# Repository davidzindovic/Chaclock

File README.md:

# Ambiental-Clock
A LED based clock that runs on the ESP8266 microcontroller. 
The 12 numbers light up depending on the time (approximation of 5 min), while the main 9 segment "picture" includes a color fade depending on the time of day.
The code includes a sleep mode , which resets the uC entirely in order to prevent the timer overflow. 
(in order to prevent any visible change upon reset - since it will most likely happen during the night)
The clock fades on sometime during the morning and fades off at a certain point during nightime.

The colors and silhuette are meant to simbolize a meditating person, relating to chakras - hence the name Chaclock.

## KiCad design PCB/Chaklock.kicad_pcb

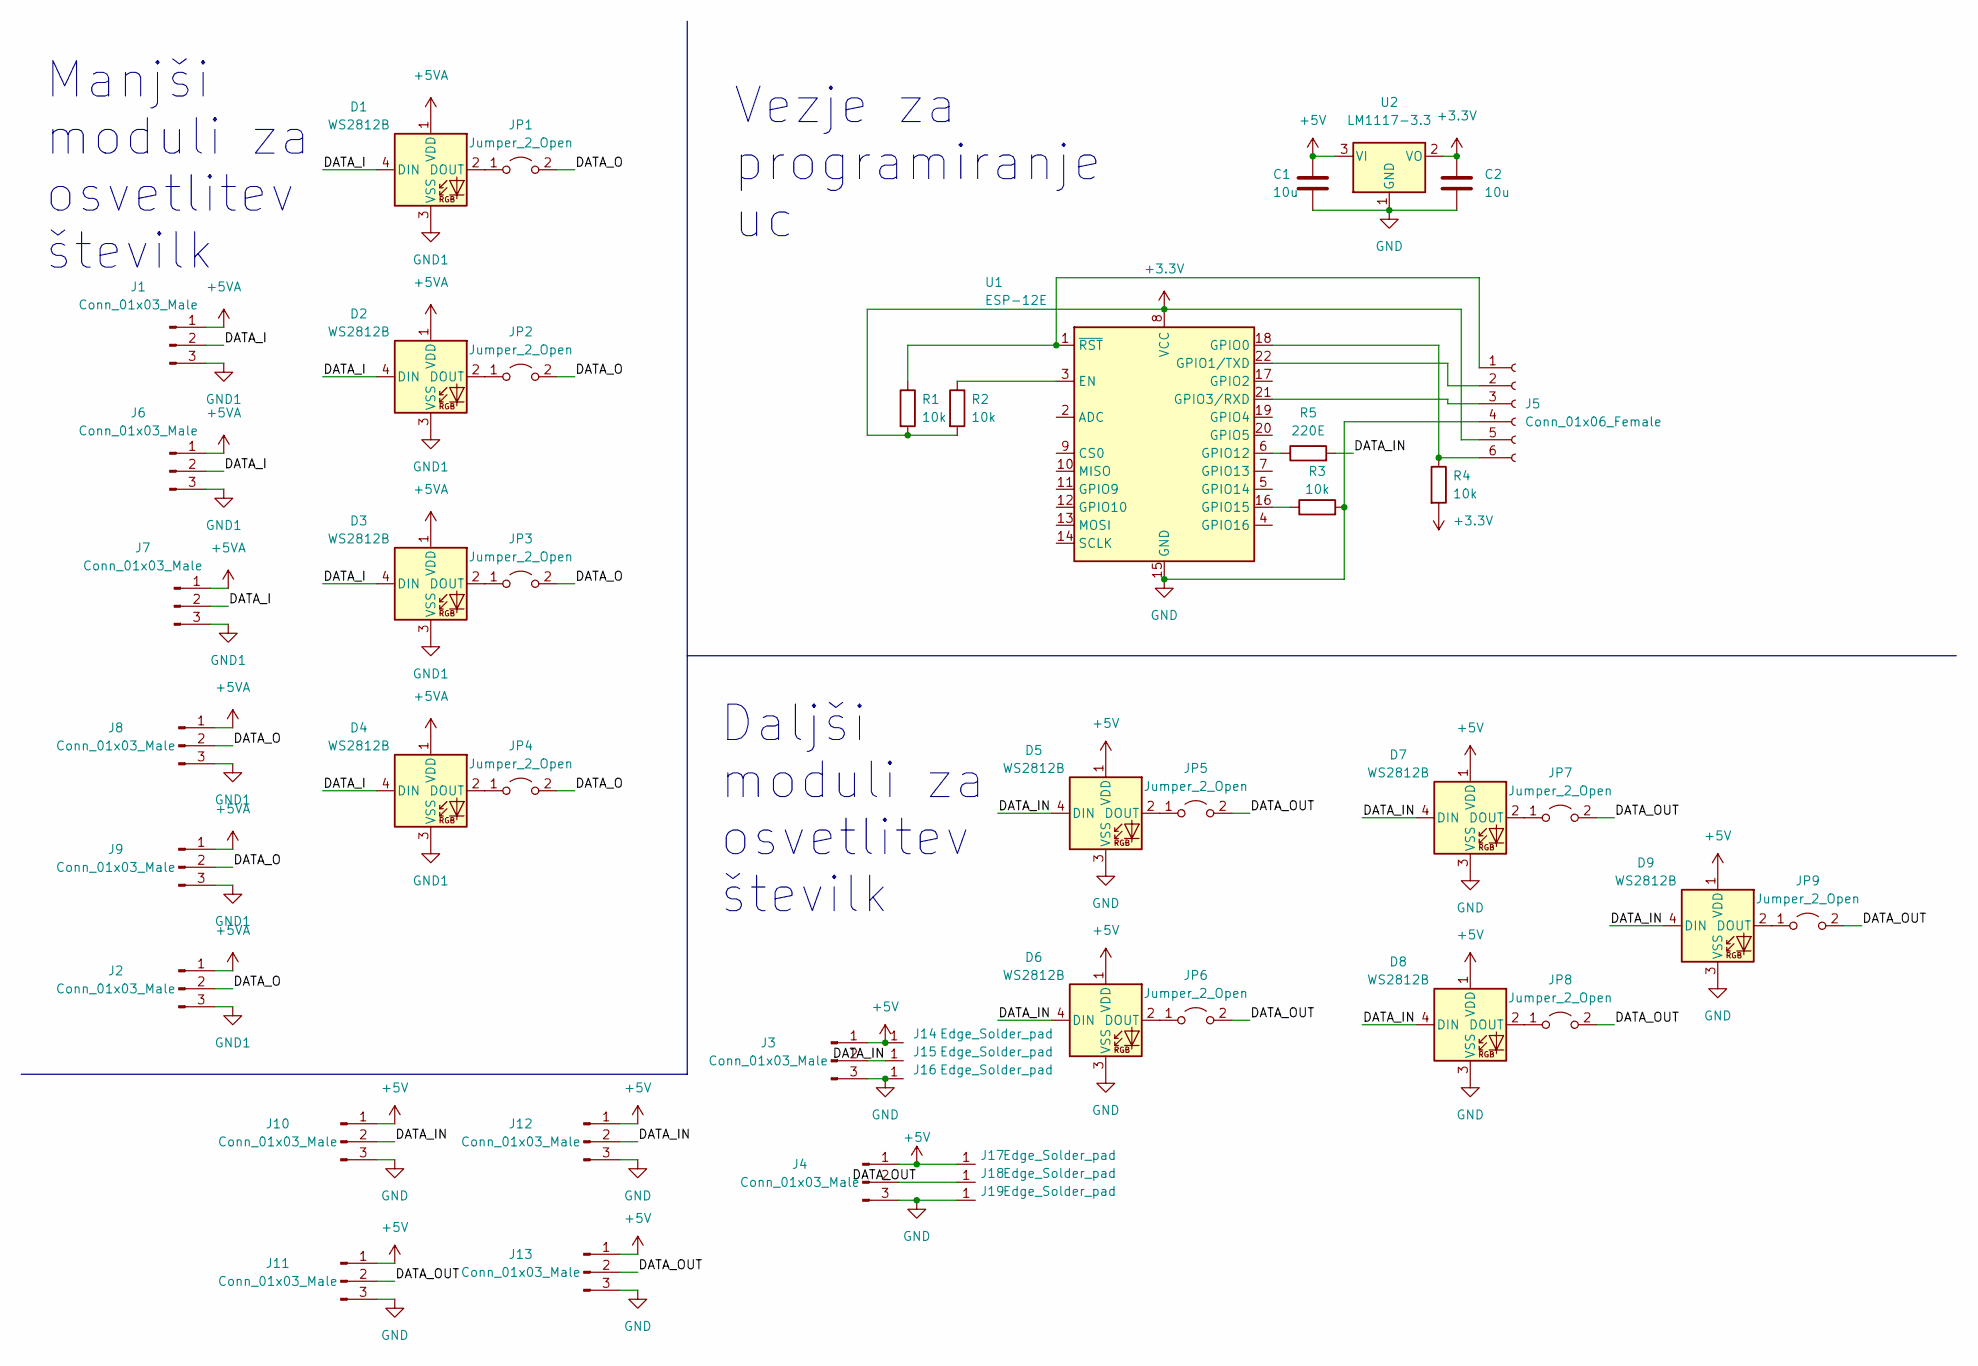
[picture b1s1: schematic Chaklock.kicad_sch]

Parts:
C1, C2: 10u; C_Disc_D5.0mm_W2.5mm_P5.00mm
D1, D2, D3, D4, D5, D6, D7, D8, D9: WS2812B; LED_WS2812B_PLCC4_5.0x5.0mm_P3.2mm
J1, J2, J3, J4, J6, J7, J8, J9, J10, J11, J12, J13: Conn_01x03_Male; PinHeader_1x03_P2.54mm_Vertical
J5: Conn_01x06_Female; PinHeader_1x06_P2.54mm_Vertical
J14, J15, J16, J17, J18, J19: Edge_Solder_pad; Edge Solder pad
JP1, JP2, JP3, JP4, JP5, JP6, JP7, JP8, JP9: Jumper_2_Open; SolderJumper-2_P1.3mm_Open_TrianglePad1.0x1.5mm
R1, R2, R3, R4: 10k; R_0805_2012Metric
R5: 220E; R_0805_2012Metric
U1: ESP-12E
U2: LM1117-3.3; TO-252-3_TabPin2

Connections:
+3.3V: C2.1, J5.5, R1.2, R2.2, R4.2, U1.8 (VCC), U2.2 (VO)
+5V: C1.1, D5.1 (VDD), D6.1 (VDD), D7.1 (VDD), D8.1 (VDD), D9.1 (VDD), J3.1, J4.1, J10.1, J11.1, J12.1, J13.1, J14.1, J17.1, U2.3 (VI)
+5VA: D1.1 (VDD), D2.1 (VDD), D3.1 (VDD), D4.1 (VDD), J1.1, J2.1, J6.1, J7.1, J8.1, J9.1
/DATA_I: D1.4 (DIN), D2.4 (DIN), D3.4 (DIN), D4.4 (DIN), J1.2, J6.2, J7.2
/DATA_IN: D5.4 (DIN), D6.4 (DIN), D7.4 (DIN), D8.4 (DIN), D9.4 (DIN), J3.2, J10.2, J12.2, J15.1, R5.2
/DATA_O: J2.2, J8.2, J9.2, JP1.2 (B), JP2.2 (B), JP3.2 (B), JP4.2 (B)
/DATA_OUT: J4.2, J11.2, J13.2, J18.1, JP5.2 (B), JP6.2 (B), JP7.2 (B), JP8.2 (B), JP9.2 (B)
GND: C1.2, C2.2, D5.3 (VSS), D6.3 (VSS), D7.3 (VSS), D8.3 (VSS), D9.3 (VSS), J3.3, J4.3, J5.4, J10.3, J11.3, J12.3, J13.3, J16.1, J19.1, R3.2, U1.15 (GND), U2.1 (GND)
GND1: D1.3 (VSS), D2.3 (VSS), D3.3 (VSS), D4.3 (VSS), J1.3, J2.3, J6.3, J7.3, J8.3, J9.3
unnamed: D1.2 (DOUT), JP1.1 (A)
unnamed: D2.2 (DOUT), JP2.1 (A)
unnamed: D3.2 (DOUT), JP3.1 (A)
unnamed: D4.2 (DOUT), JP4.1 (A)
unnamed: D5.2 (DOUT), JP5.1 (A)
unnamed: D6.2 (DOUT), JP6.1 (A)
unnamed: D7.2 (DOUT), JP7.1 (A)
unnamed: D8.2 (DOUT), JP8.1 (A)
unnamed: D9.2 (DOUT), JP9.1 (A)
unnamed: J5.1, R1.1, U1.1 (~RST)
unnamed: J5.2, U1.22 (GPIO1/TXD)
unnamed: J5.3, U1.21 (GPIO3/RXD)
unnamed: J5.6, R4.1, U1.18 (GPIO0)
unnamed: R2.1, U1.3 (EN)
unnamed: R3.1, U1.16 (GPIO15)
unnamed: R5.1, U1.6 (GPIO12)

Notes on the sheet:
Vezje za programiranje uc
Daljši moduli za osvetlitev številk
Manjši moduli za osvetlitev številk

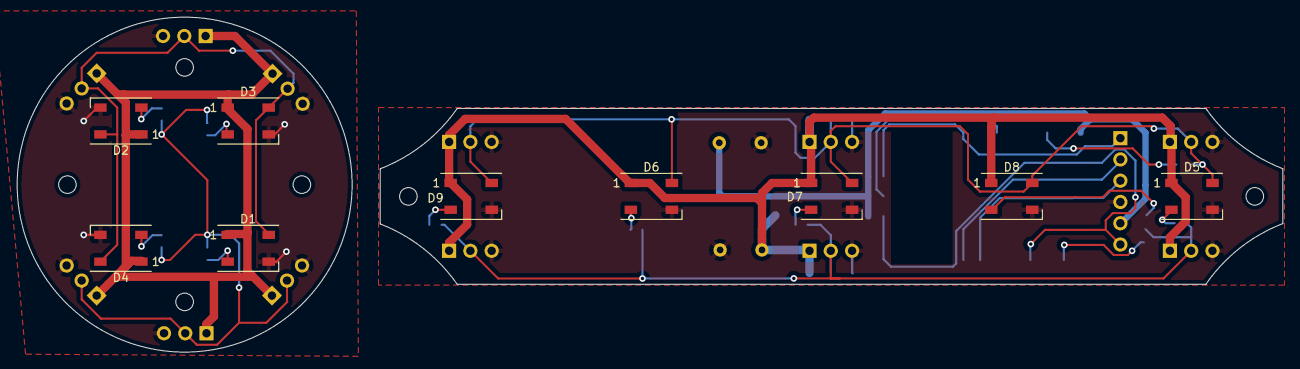
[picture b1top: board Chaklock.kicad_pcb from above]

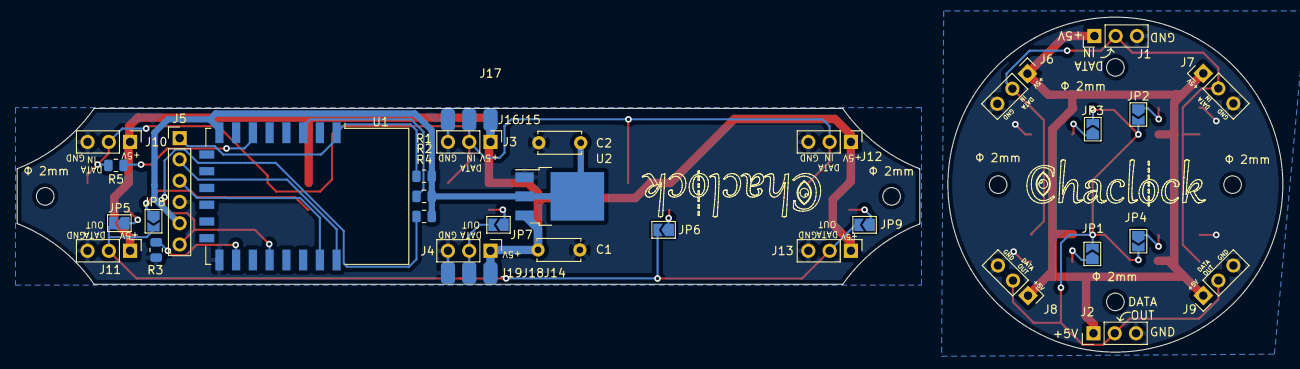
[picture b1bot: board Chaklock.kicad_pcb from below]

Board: 2 copper layers, 151.2 x 40.0 mm, 52 parts (37 on the bottom side), 25 nets.

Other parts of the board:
Ф 2mm, Ф 2mm#2, Ф 2mm#3, Ф 2mm#4, Ф 2mm#5, Ф 2mm#6: MountingHole_2.1mm

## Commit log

2021-12-26 Create main_code
2022-11-18 Update main_code
2025-06-13 Rename Logo.dxf to Graphics/Logo.dxf
2025-06-13 Rename Logo2.dxf to Graphics/Logo2.dxf
2025-06-13 Rename Logo3.dxf to Graphics/Logo3.dxf
2025-06-13 Rename chakra grafika back plate.dxf to Graphics/chakra grafika back plate.dxf
2025-06-13 Rename chakra grafika back plate.svg to Graphics/chakra grafika back plate.svg
2025-06-13 Rename Logo chaclock.dxf to Graphics/Logo chaclock.dxf
2025-06-13 Rename Logo chaclock.svg to Graphics/Logo chaclock.svg
2025-06-13 Rename Chaklock.kicad_pro to PCB/Chaklock.kicad_pro
2025-06-13 Rename 3D model.zip to 3D models/3D model.zip
2025-06-13 Rename Chaclock Assembly.png to 3D models/Chaclock Assembly.png
2025-06-13 Rename main_code to code/main_code
2025-06-13 Rename Chaclock Assembly.png to Chaclock_Assembly.png
